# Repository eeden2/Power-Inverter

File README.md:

# Power-Inverter
This board is intended to be an FPGA based approach with a Unipolar Power Inverter. 
Simply plug in a 12V source like a car battery and out comes a safe 120V AC voltage.
# Simulation
Simulations were made with Simulink to further the decision concerning the power filters of the Unipolar H-Bridge.

# Updates
Fixes to the Netlist in KiCAD are still required for ease of design in future iterations.
 
# 3D - View

# PCB

# Schematic

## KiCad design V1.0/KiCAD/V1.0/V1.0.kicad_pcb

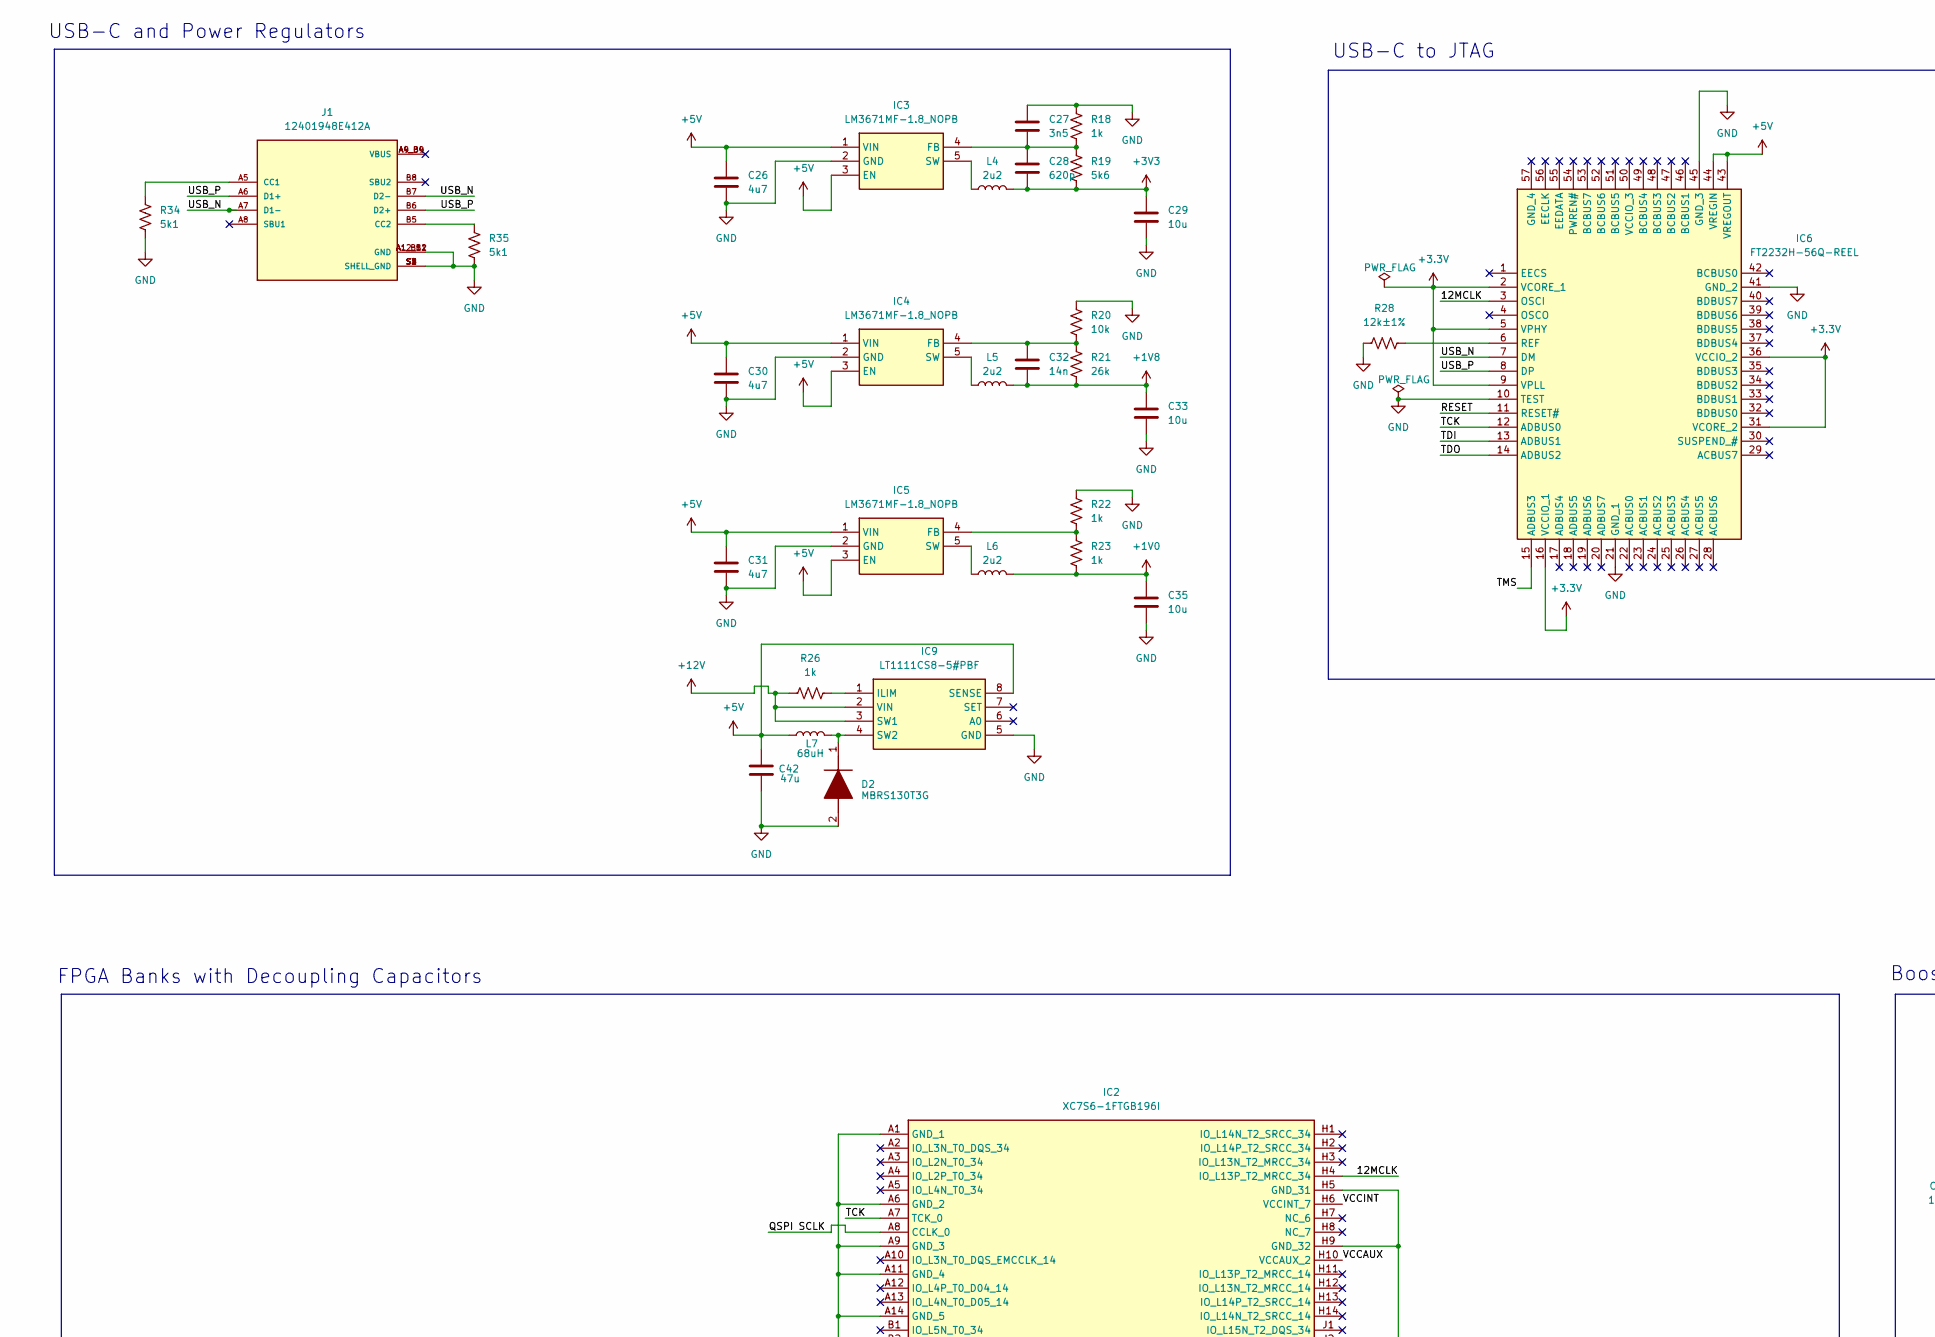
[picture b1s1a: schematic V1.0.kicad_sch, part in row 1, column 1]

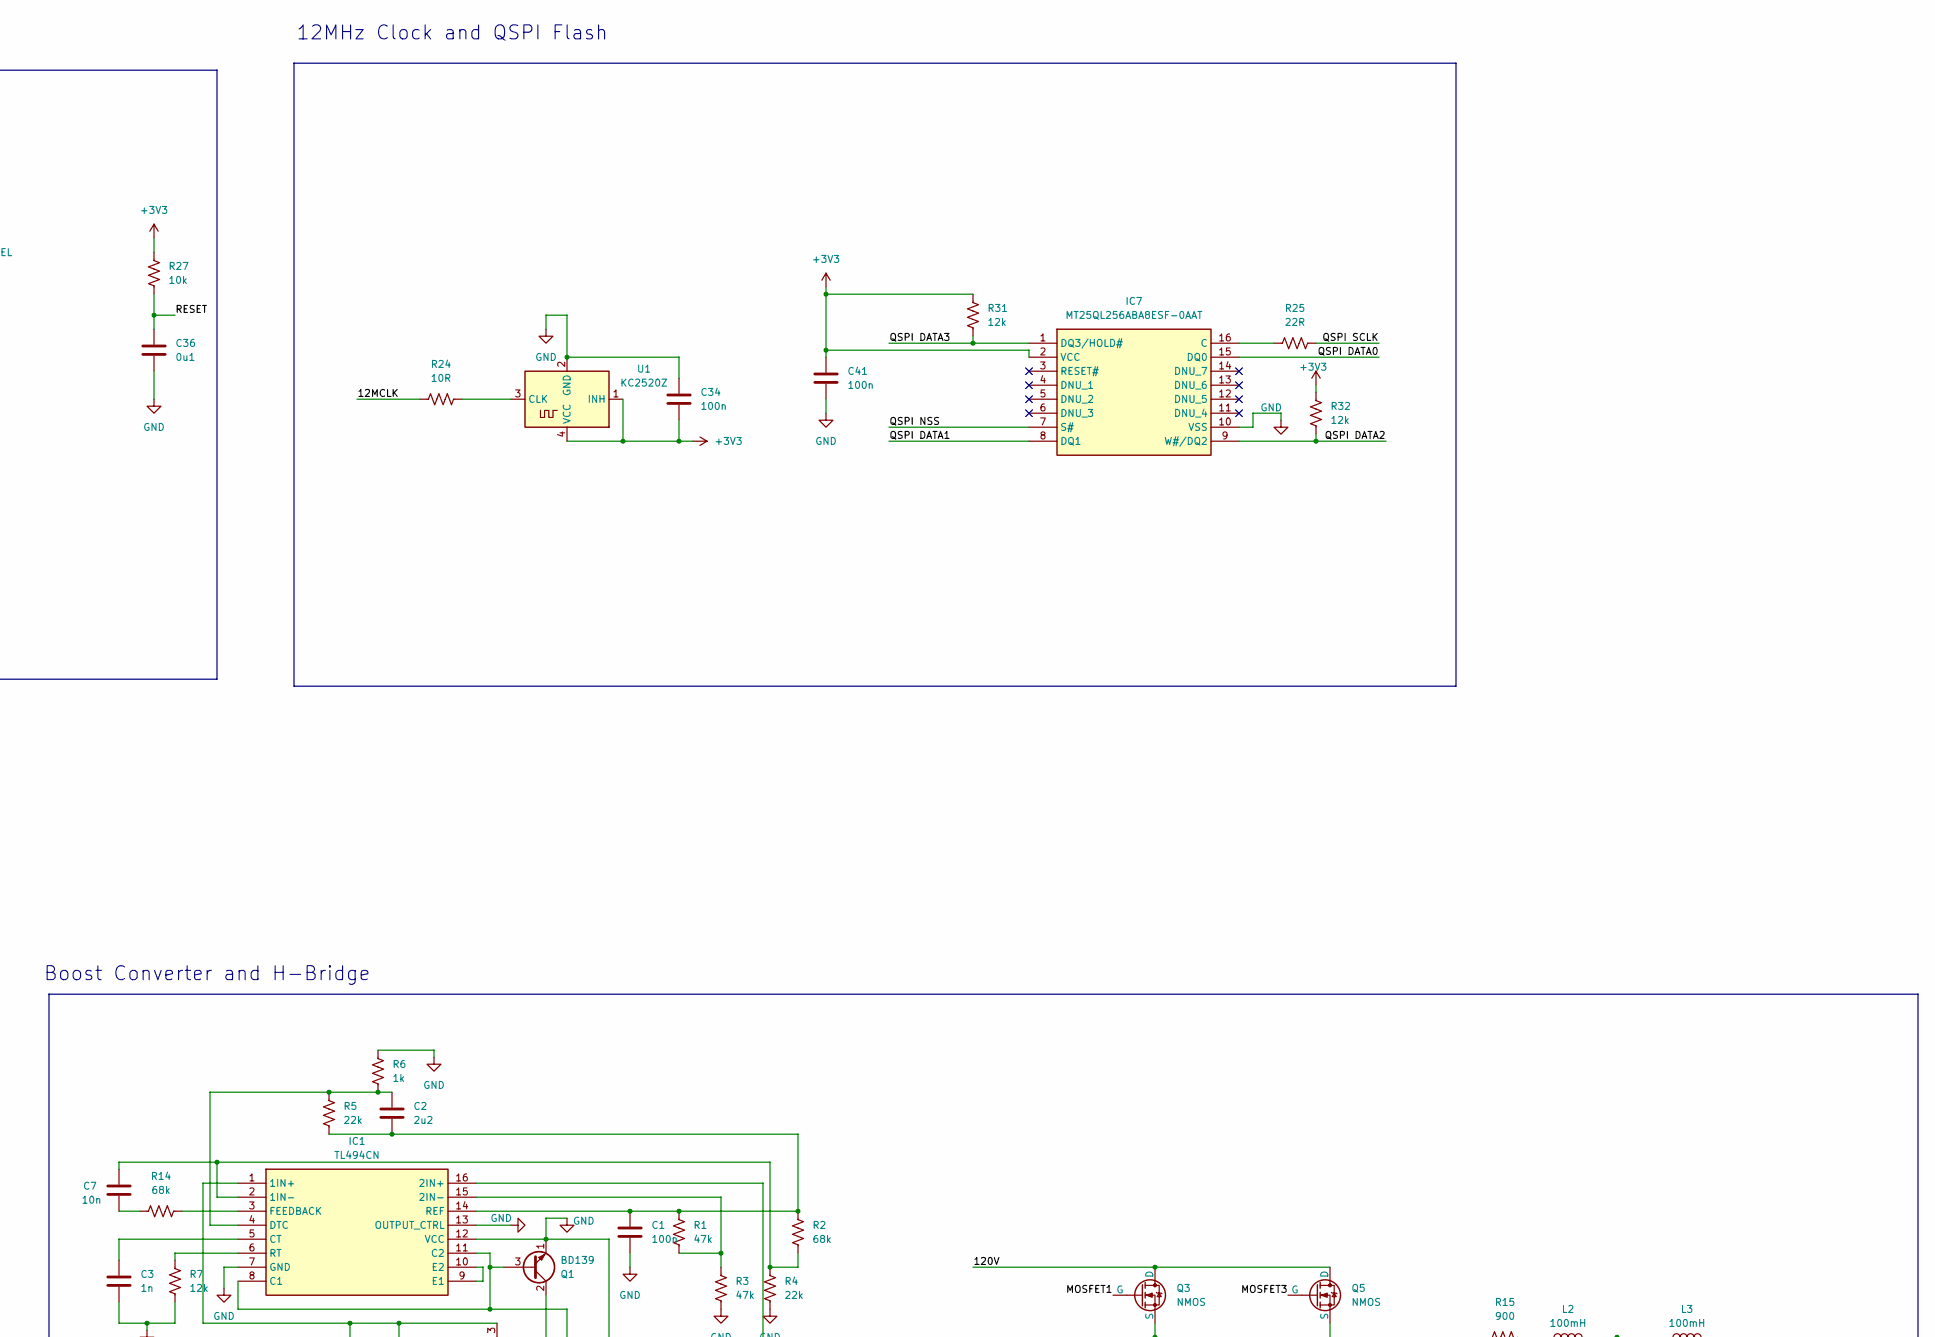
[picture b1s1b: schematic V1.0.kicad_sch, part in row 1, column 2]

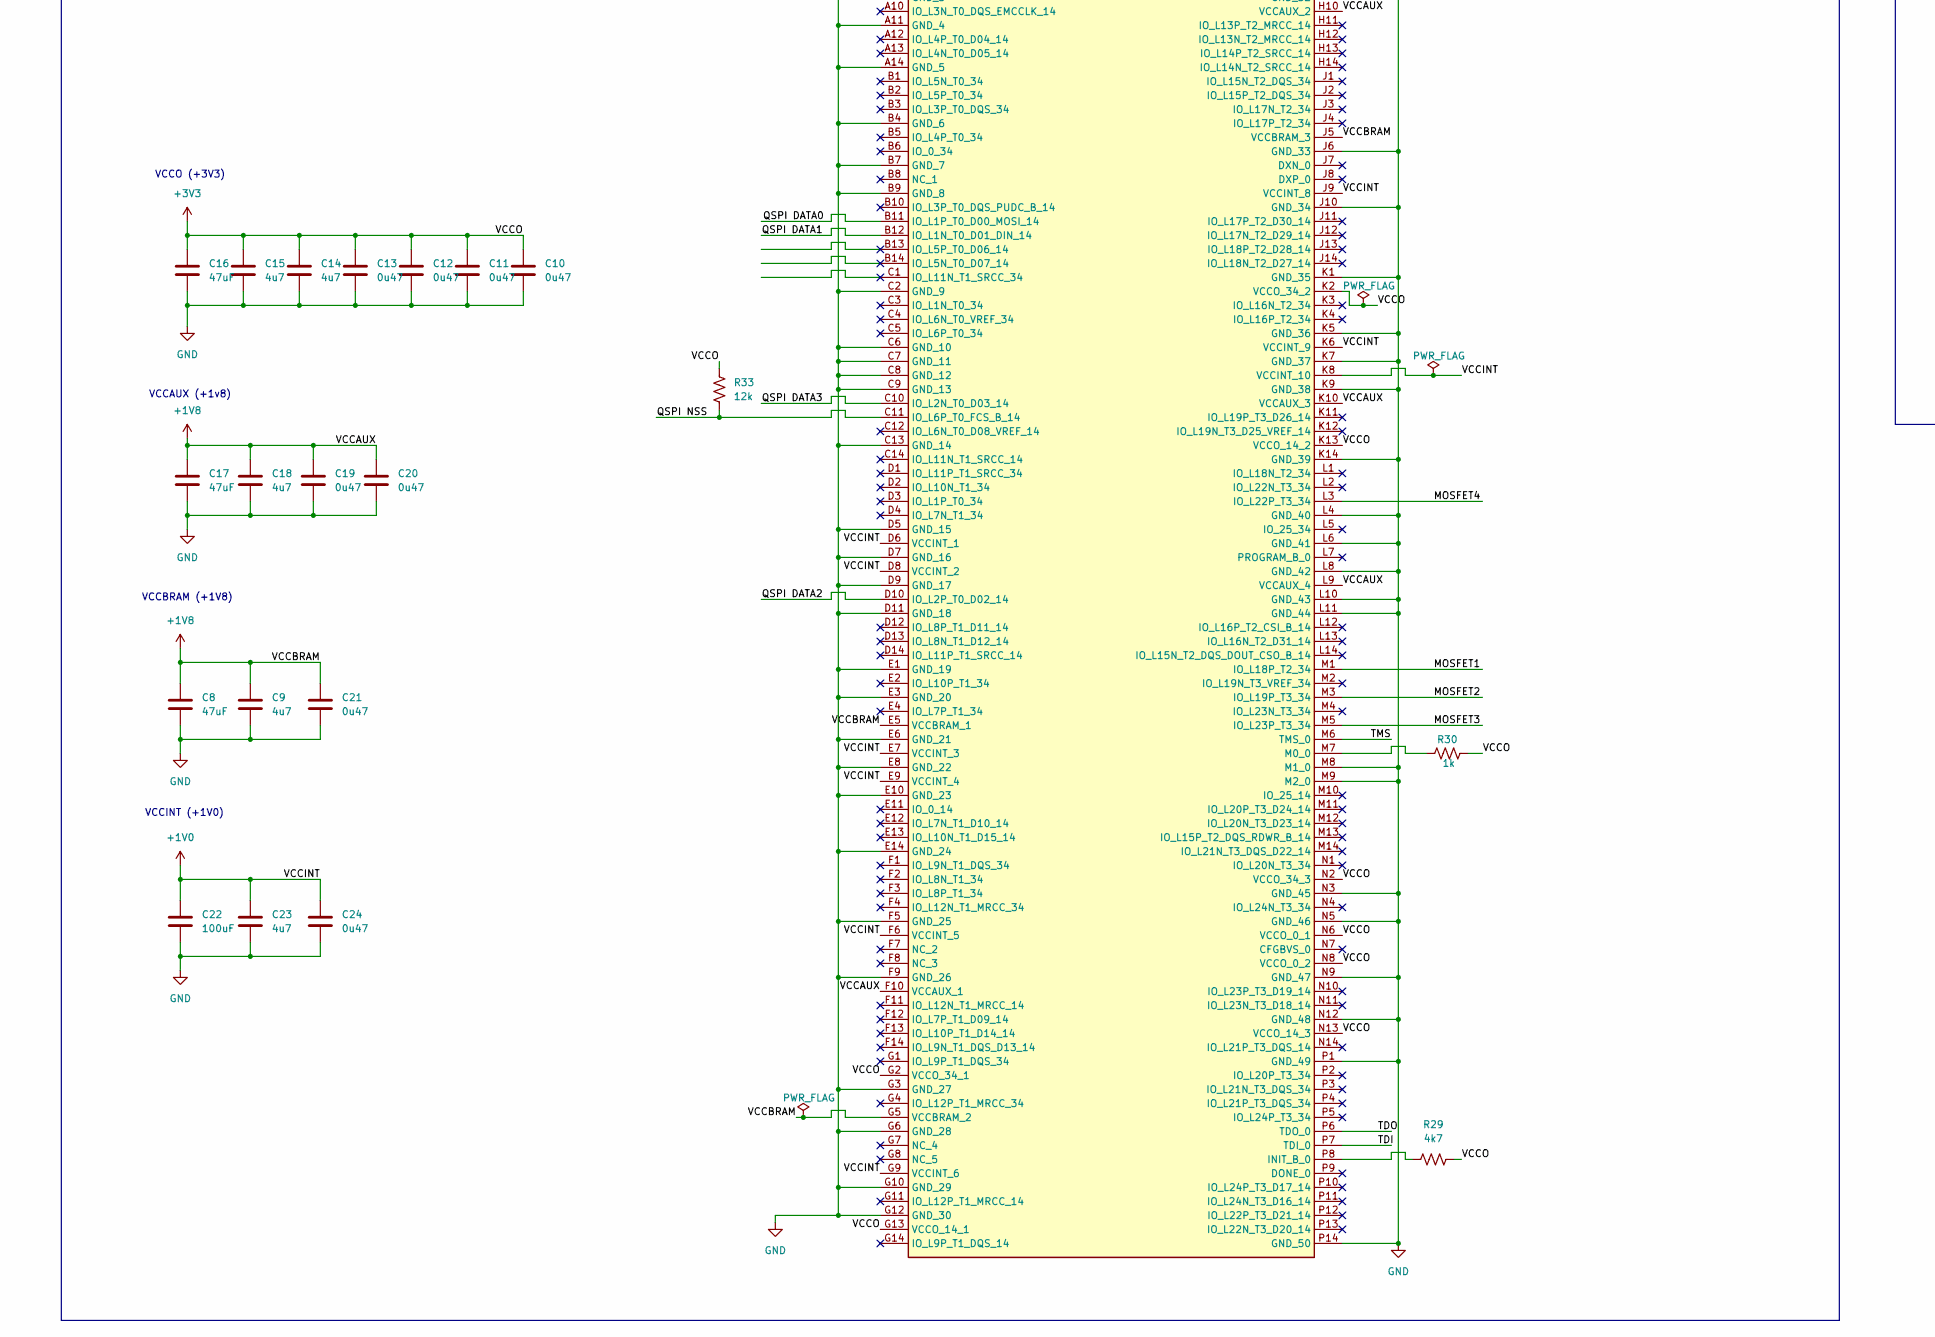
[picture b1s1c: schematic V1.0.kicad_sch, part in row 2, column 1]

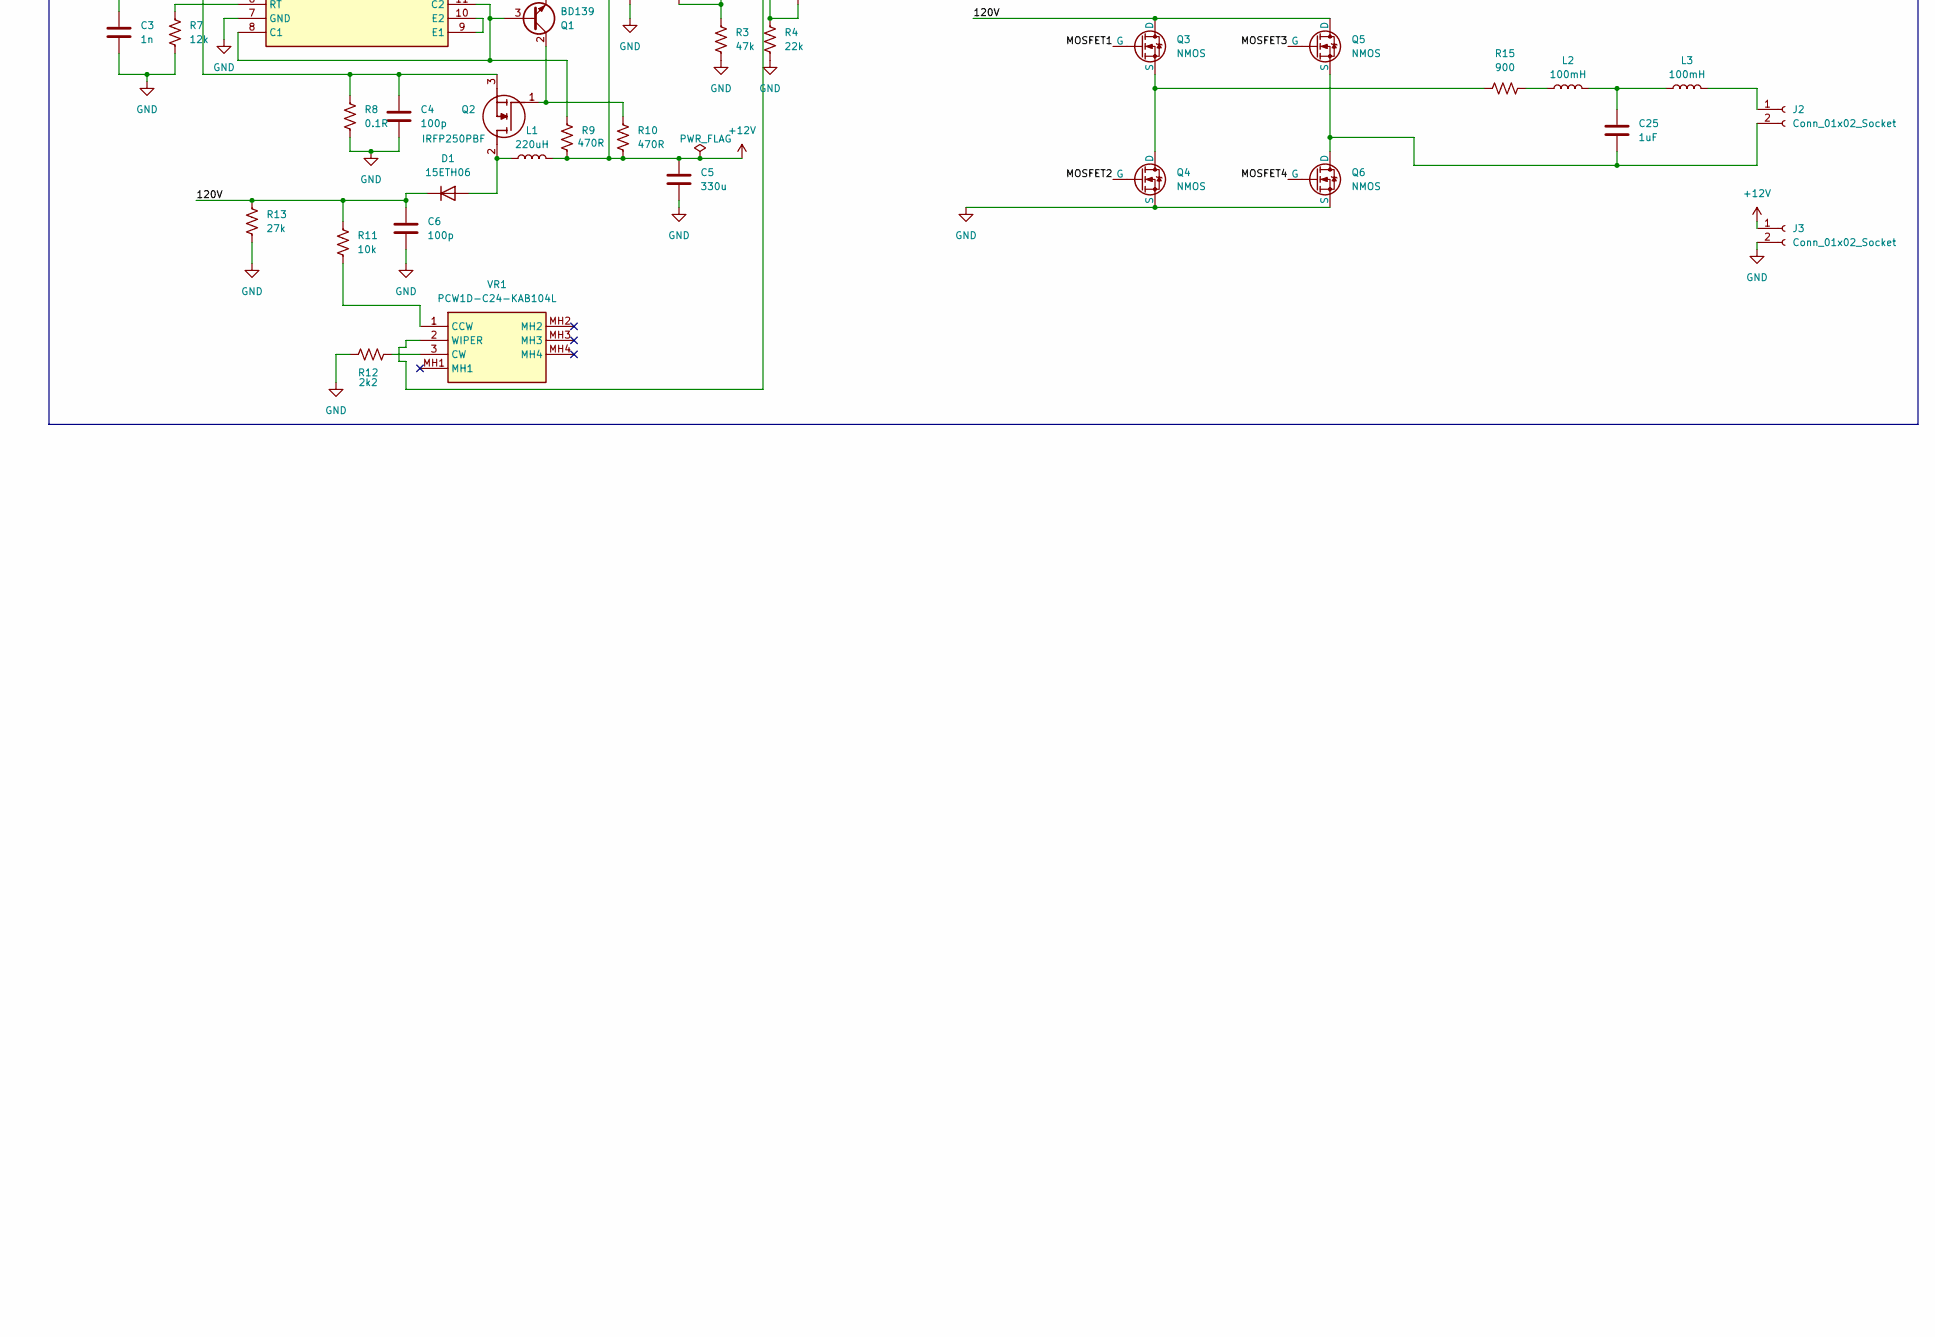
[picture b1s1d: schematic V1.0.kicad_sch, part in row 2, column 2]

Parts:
C1, C34, C41: 100n; CAPC1608X90N
C2: 2u2; CAPC2012X140N
C3: 1n; CAPC2012X94N
C4, C6: 100p; CAPC1005X55N
C5: 330u; C0805
C7: 10n; CAPC1608X90N
C8, C16, C17: 47uF; CAPC2012X145N
C9, C14, C15, C18, C23, C26, C30, C31: 4u7; CAPC1608X100N
C10, C11, C12, C13, C19, C20, C21, C24: 0u47; CAPC3216X152N
C22: 100uF; CAPPRD350W60D850H1300
C25: 1uF; CAPC0603X39N
C27: 3n5; C0805
C28: 620p; CAPC1608X87N
C29, C33, C35: 10u; CAPC3225X178N
C32: 14n; CAPC5750X550N
C36: 0u1; CAPC1608X90N
C42: 47u; CAPC2012X145N
D1: 15ETH06; TO508P465X1031X1932-2P
D2: MBRS130T3G; DIOM5436X247N; Mouser Part Number 863-MBRS130T3G
IC1: TL494CN; DIP794W53P254L1930H508Q16N; Mouser Part Number 595-TL494CN
IC2: XC7S6-1FTGB196I; BGA196C100P14X14_1500X1500X155; Mouser Part Number 217-XC7S6-1FTGB196I
IC3, IC4, IC5: LM3671MF-1.8_NOPB; SOT95P280X145-5N; Mouser Part Number 926-LM3671MF-1.8NOPB
IC6: FT2232H-56Q-REEL; QFN50P800X800X100-57N-D; Mouser Part Number 895-FT2232H-56Q-REEL
IC7: MT25QL256ABA8ESF-0AAT; SOIC127P1032X265-16N; Mouser Part Number 340-279831-TRAY
IC9: LT1111CS8-5#PBF; SOIC127P599X175-8N; Mouser Part Number 584-LT1111CS8-5#PBF
J1: 12401948E412A; AMPHENOL_12401948E412A; PARTREV 3
J2, J3: Conn_01x02_Socket; PhoenixContact_MSTBA_2,5_2-G_1x02_P5.00mm_Horizontal
L1: 220uH; SRR5228A
L2, L3: 100mH; CAPPRD600W90D1200H2100
L4, L5, L6: 2u2; RCH875NP2R2M
L7: 68uH; WE-TI_809589
Q1: BD139; TO-126-3_Vertical
Q2: IRFP250PBF; TO254P465X1024X2050-3P; Mouser Part Number 844-IRFP250PBF
Q3, Q4, Q5, Q6: NMOS; TO254P465X1024X2050-3P
R1, R3: 47k; RESC1005X37N
R2: 68k; ERJUP6
R4, R5: 22k; ERA8KEB1004V
R6, R18, R22, R23, R26: 1k; RESC3016X58N
R7, R31, R32, R33: 12k; ERA8KEB1004V
R8: 0.1R; RESC15077X100N
R9, R10: 470R; ERA8KEB1004V
R11, R20, R27: 10k; RESC1005X37N
R12: 2k2; RESC1005X40N
R13: 27k; ERJUP6
R14: 68k; ERJ1GJJ2R4C
R15: 900; RESC3116X65N
R19: 5k6; ERA2AED122X
R21: 26k; ERA2AED122X
R24: 10R; RESC3216X65N
R25: 22R; RESC3116X65N
R28: 12k±1%; ERA8KEB1004V
R29: 4k7; ERA3AEB101V
R30: 1k; ERA8KEB1004V
R34, R35: 5k1; ERJUP6
U1: KC2520Z; Oscillator_SMD_Kyocera_KC2520Z-4Pin_2.5x2.0mm
VR1: PCW1D-C24-KAB104L; PCW1DC24KAB104L; Manufacturer_Part_Number PCW1D-C24-KAB104L

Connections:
+1V0: C22.1, C23.1, C24.1, C35.1, IC2.D6 (VCCINT_1), IC2.D8 (VCCINT_2), IC2.E7 (VCCINT_3), IC2.E9 (VCCINT_4), IC2.F6 (VCCINT_5), IC2.G9 (VCCINT_6), IC2.H6 (VCCINT_7), IC2.J9 (VCCINT_8), IC2.K6 (VCCINT_9), IC2.K8 (VCCINT_10), L6.2, R23.2
+1V8: C8.1, C9.1, C17.1, C18.1, C19.1, C20.1, C21.1, C32.2, C33.1, IC2.E5 (VCCBRAM_1), IC2.F10 (VCCAUX_1), IC2.G5 (VCCBRAM_2), IC2.H10 (VCCAUX_2), IC2.J5 (VCCBRAM_3), IC2.K10 (VCCAUX_3), IC2.L9 (VCCAUX_4), L5.2, R21.2
+5V: C26.1, C30.1, C31.1, C42.1, IC3.1 (VIN), IC3.3 (EN), IC4.1 (VIN), IC4.3 (EN), IC5.1 (VIN), IC5.3 (EN), IC6.43 (VREGOUT), IC6.44 (VREGIN), IC9.8 (SENSE), L7.1
+12V: C1.2, C3.2, C4.2, C5.1, C5.2, C6.2, C8.2, C9.2, C10.2, C11.2, C12.2, C13.2, C14.2, C15.2, C16.2, C17.2, C18.2, C19.2, C20.2, C21.2, C22.2, C23.2, C24.2, C26.2, C27.1, C29.2, C30.2, C31.2, C33.2, C34.1, C35.2, C36.2, C41.2, C42.2, D2.2 (A), IC1.7 (GND), IC1.12 (VCC), IC1.13 (OUTPUT_CTRL), IC2.A1 (GND_1), IC2.A6 (GND_2), IC2.A9 (GND_3), IC2.A11 (GND_4), IC2.A14 (GND_5), IC2.B4 (GND_6), IC2.B7 (GND_7), IC2.B9 (GND_8), IC2.C2 (GND_9), IC2.C6 (GND_10), IC2.C7 (GND_11), IC2.C8 (GND_12), IC2.C9 (GND_13), IC2.C13 (GND_14), IC2.D5 (GND_15), IC2.D7 (GND_16), IC2.D9 (GND_17), IC2.D11 (GND_18), IC2.E1 (GND_19), IC2.E3 (GND_20), IC2.E6 (GND_21), IC2.E8 (GND_22), IC2.E10 (GND_23), IC2.E14 (GND_24), IC2.F5 (GND_25), IC2.F9 (GND_26), IC2.G3 (GND_27), IC2.G6 (GND_28), IC2.G10 (GND_29), IC2.G12 (GND_30), IC2.H5 (GND_31), IC2.H9 (GND_32), IC2.J6 (GND_33), IC2.J10 (GND_34), IC2.K1 (GND_35), IC2.K5 (GND_36), IC2.K7 (GND_37), IC2.K9 (GND_38), IC2.K14 (GND_39), IC2.L4 (GND_40), IC2.L6 (GND_41), IC2.L8 (GND_42), IC2.L10 (GND_43), IC2.L11 (GND_44), IC2.M8 (M1_0), IC2.M9 (M2_0), IC2.N3 (GND_45), IC2.N5 (GND_46), IC2.N9 (GND_47), IC2.N12 (GND_48), IC2.P1 (GND_49), IC2.P14 (GND_50), IC3.2 (GND), IC4.2 (GND), IC5.2 (GND), IC6.10 (TEST), IC6.21 (GND_1), IC6.41 (GND_2), IC6.45 (GND_3), IC7.10 (VSS), IC9.2 (VIN), IC9.3 (SW1), IC9.5 (GND), J1.A1_B12 (GND), J1.A12_B1 (GND), J1.S1 (SHELL_GND), J1.S2 (SHELL_GND), J1.S3 (SHELL_GND), J1.S4 (SHELL_GND), J3.1, J3.2, L1.2, Q1.1 (E), Q4.3 (S), Q6.3 (S), R3.2, R4.2, R6.2, R7.2, R8.2, R9.2, R10.2, R12.2, R13.2, R18.1, R20.1, R22.1, R26.1, R28.1, R34.2, R35.2, U1.2 (GND)
/12MCLK: IC2.H4 (IO_L13P_T2_MRCC_34), IC6.3 (OSCI), R24.2
/120V: C6.1, D1.1 (K), Q3.1 (D), Q5.1 (D), R11.1, R13.1
/MOSFET1: IC2.M1 (IO_L18P_T2_34), Q3.2 (G)
/MOSFET2: IC2.M3 (IO_L19P_T3_34), Q4.2 (G)
/MOSFET3: IC2.M5 (IO_L23P_T3_34), Q5.2 (G)
/MOSFET4: IC2.L3 (IO_L22P_T3_34), Q6.2 (G)
/QSPI DATA0: IC2.B11 (IO_L1P_T0_D00_MOSI_14), IC7.15 (DQ0)
/QSPI DATA1: IC2.B12 (IO_L1N_T0_D01_DIN_14), IC7.8 (DQ1)
/QSPI DATA2: IC2.D10 (IO_L2P_T0_D02_14), IC7.9 (W#/DQ2), R32.1
/QSPI DATA3: IC2.C10 (IO_L2N_T0_D03_14), IC7.1 (DQ3/HOLD#), R31.1
/QSPI NSS: IC2.C11 (IO_L6P_T0_FCS_B_14), IC7.7 (S#), R33.1
/QSPI SCLK: IC2.A8 (CCLK_0), R25.2
/RESET: C36.1, IC6.11 (RESET#), R27.2
/TCK: IC2.A7 (TCK_0), IC6.12 (ADBUS0)
/TDI: IC2.P7 (TDI_0), IC6.13 (ADBUS1)
/TDO: IC2.P6 (TDO_0), IC6.14 (ADBUS2)
/TMS: IC2.M6 (TMS_0), IC6.15 (ADBUS3)
/USB_N: IC6.7 (DM), J1.A7 (D1-), J1.B7 (D2-)
/USB_P: IC6.8 (DP), J1.A6 (D1+), J1.B6 (D2+)
unnamed: C7.2, R14.1
unnamed: C25.1, L2.2, L3.1
unnamed: D1.2 (A), L1.1, Q2.2 (D)
unnamed: D2.1 (K), IC9.4 (SW2), L7.2
unnamed: C4.1, IC1.1 (1IN+), Q2.3 (S), R8.1
unnamed: C7.1, IC1.2 (1IN-), R2.2, R4.1
unnamed: IC1.16 (2IN+), VR1.2 (WIPER)
unnamed: IC1.15 (2IN-), R1.2, R3.1
unnamed: IC1.8 (C1), IC1.11 (C2), Q1.3 (B), R9.1
unnamed: C3.1, IC1.5 (CT)
unnamed: C2.1, IC1.4 (DTC), R5.1, R6.1
unnamed: IC1.9 (E1), IC1.10 (E2)
unnamed: IC1.3 (FEEDBACK), R14.2
unnamed: C1.1, C2.2, IC1.14 (REF), R1.1, R2.1, R5.2
unnamed: IC1.6 (RT), R7.1
unnamed: IC2.P8 (INIT_B_0), R29.1
unnamed: IC2.M7 (M0_0), R30.1
unnamed: C27.2, C28.1, IC3.4 (FB), R18.2, R19.1
unnamed: IC3.5 (SW), L4.1
unnamed: C32.1, IC4.4 (FB), R20.2, R21.1
unnamed: IC4.5 (SW), L5.1
unnamed: IC5.4 (FB), R22.2, R23.1
unnamed: IC5.5 (SW), L6.1
unnamed: IC6.6 (REF), R28.2
unnamed: IC7.16 (C), R25.1
unnamed: IC9.1 (ILIM), R26.2
unnamed: J1.A5 (CC1), R34.1
unnamed: J1.B5 (CC2), R35.1
unnamed: J2.1, L3.2
unnamed: C25.2, J2.2, Q5.3 (S), Q6.1 (D)
unnamed: L2.1, R15.2
unnamed: Q1.2 (C), Q2.1 (G), R10.1
unnamed: Q3.3 (S), Q4.1 (D), R15.1
unnamed: R24.1, U1.3 (CLK)
unnamed: R11.2, VR1.1 (CCW)
unnamed: R12.1, VR1.3 (CW)

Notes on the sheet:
Boost Converter and H-Bridge
VCCO (+3V3)
USB-C and Power Regulators
VCCINT (+1V0)
USB-C to JTAG
VCCBRAM (+1V8)
VCCAUX (+1v8)
12MHz Clock and QSPI Flash
FPGA Banks with Decoupling Capacitors

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
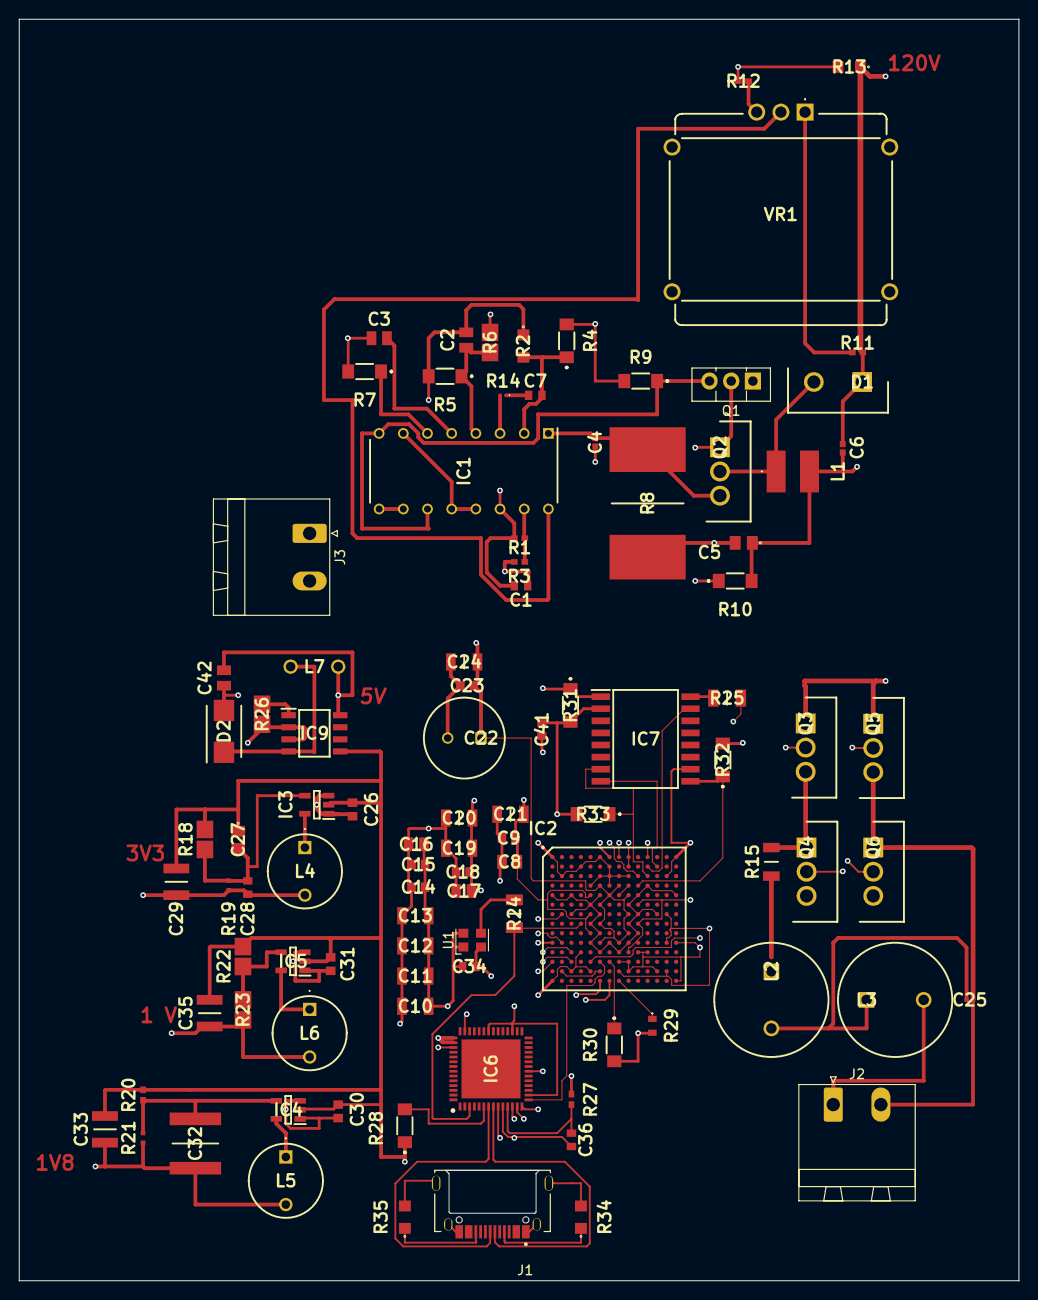
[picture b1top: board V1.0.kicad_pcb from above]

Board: 4 copper layers, 105.0 x 132.5 mm, 99 parts (0 on the bottom side), 61 nets.

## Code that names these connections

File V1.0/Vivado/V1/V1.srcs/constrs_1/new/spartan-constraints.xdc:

#CLOCK
set_property -dict {PACKAGE_PIN H4 IOSTANDARD LVCMOS33} {get_ports {CLK12MHZ}};
create_clock -add -name sys_clk -period 83.333 -waveform {0 41.667} {get_ports {CLK12MHZ}};

#MOSFET1
set_property -dict {PACKAGE_PIN M1 IOSTANDARD LVCMOS33} {get_ports {MOSFET1}};

#MOSFET2
set_property -dict {PACKAGE_PIN M3 IOSTANDARD LVCMOS33} {get_ports {MOSFET2}};

#MOSFET3
set_property -dict {PACKAGE_PIN M5 IOSTANDARD LVCMOS33} {get_ports {MOSFET3}};

#MOSFET4
set_property -dict {PACKAGE_PIN L3 IOSTANDARD LVCMOS33} {get_ports {MOSFET4}};

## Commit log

2024-07-07 More Parts added to the Schematic
2024-07-18 Schematic is Finished
2024-07-26 Update to Codebase.
2024-08-07 Update To Schematic
2024-08-07 Schematic
2024-08-14 PCB Design is almost finished.
2024-08-16 Added Images
2024-09-02 Finished the PCB Design!
